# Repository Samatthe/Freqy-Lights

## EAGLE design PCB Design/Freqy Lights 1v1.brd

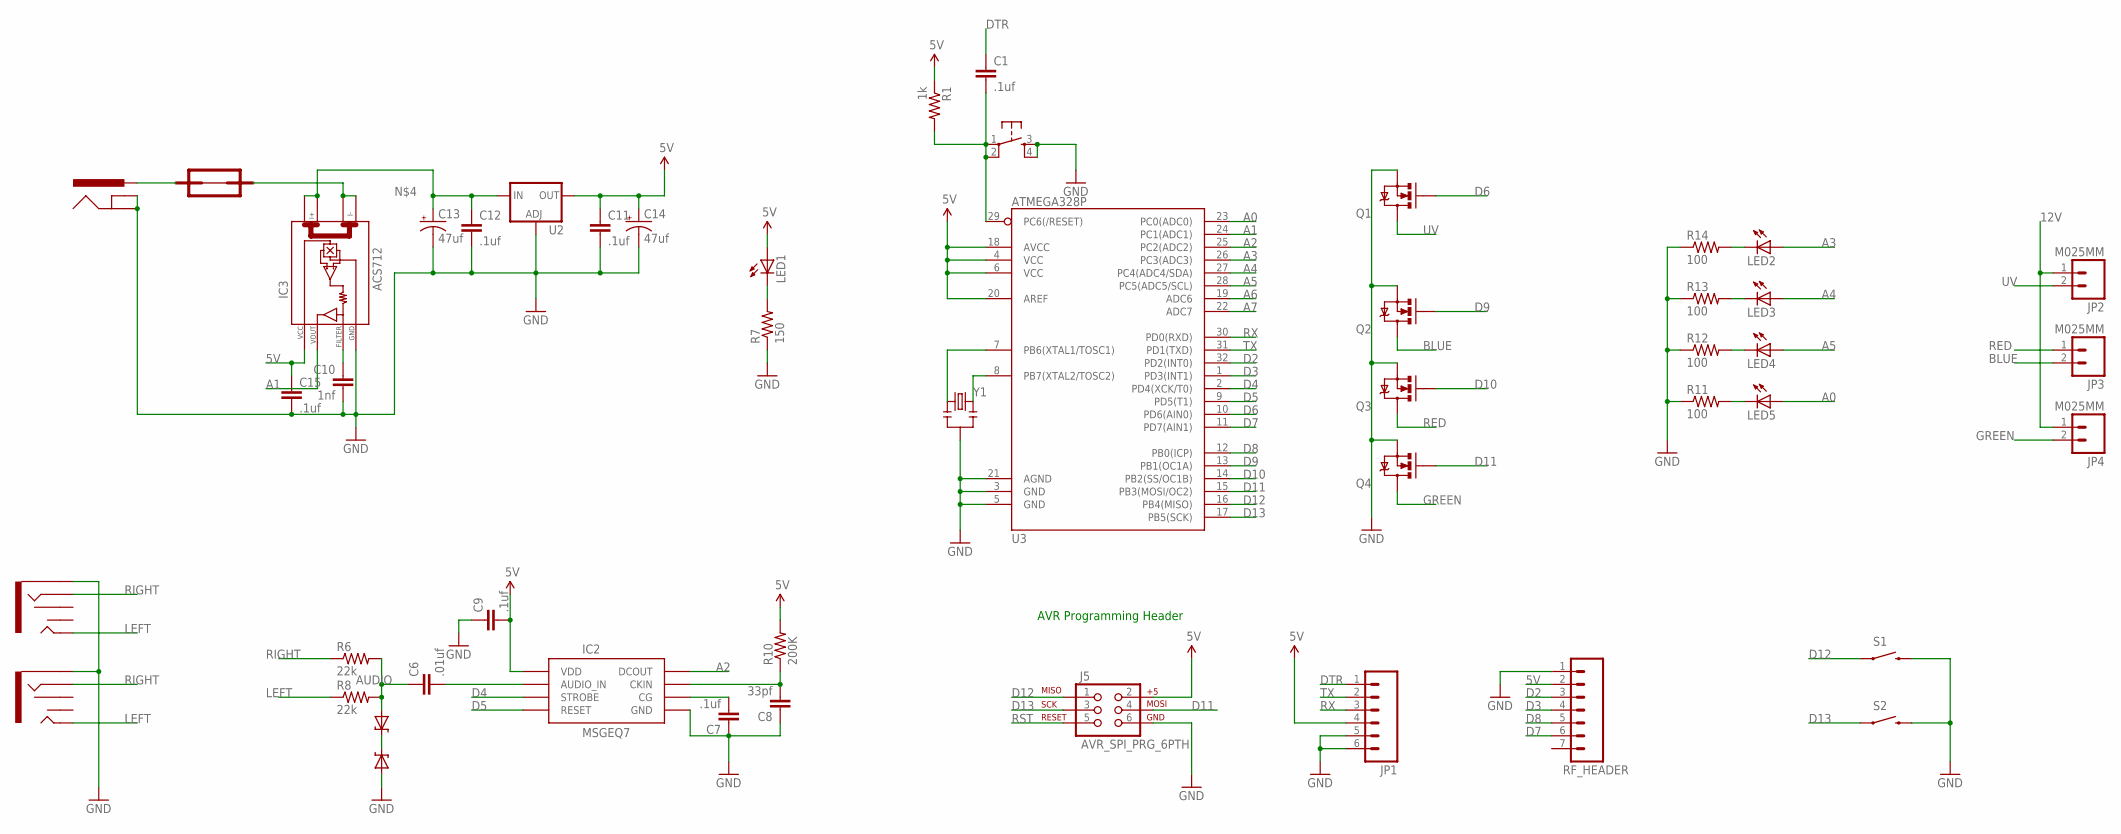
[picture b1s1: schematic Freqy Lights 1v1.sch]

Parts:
AJ1, AJ2: SC1488-1-ND_SMD_AUDIO_3.5; 3.5MM_SMD_AUDIO_SC1488-1-ND
BJ1: CP-202BH-ND_POWERJACK; POWER_JACK_CP-202BH-ND
C1, C7, C9, C11, C12, C15: .1uf; 1206
C6: .01uf; 1206
C8: 33pf; 1206
C10: 1nf; 1206
C13, C14: 47uf; SMD_47UF_CAP_493-2202-1-ND
F1: SSQ12
IC2: MSGEQ7SOIC; SOIC8
IC3: ACS712; SO08
J5: AVR_SPI_PRG_6PTH; 2X3
JP1: M06SIP; 1X06
JP2, JP3, JP4: M025MM; SCREWTERMINAL-5MM-2
LED1, LED2, LED3, LED4, LED5: LED1206; LED-1206
P1: CKN9085CT-ND_SMT_PUSHBUTTON; SMT_PUSHBUTTON_CKN9085CT-ND
Q1, Q2, Q3, Q4: MOSFET-NCHANNELBSS138; SOT23
R1: 1k; 1206
R6, R8: 22k; 1206
R7: 150; 1206
R10: 200K; 1206
R11, R12, R13, R14: 100; 1206
RF_HEADER: M07; 1X07
S1, S2: SWITCH-MOMENTARY-2PTH; TACTILE-PTH
U2: V_REG_317SMD; SOT223
U3: ATMEGA328P; TQFP32-08
U$10, U$11: MM3Z3V3ST1GOSCT-ND_3V_DIODE; 3V_DIODE_MM3Z3V3ST1GOSCT-ND
Y1: RESONATORPTH; RESONATOR-PTH

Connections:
5V: C9.2, C11.1, C14.P$2 (+), C15.1, IC2.1 (VDD), IC3.8 (VCC), J5.2, JP1.4, LED1.A, R1.1, R10.2, RF_HEADER.2, U2.2 (OUT), U3.4 (VCC), U3.6 (VCC), U3.18 (AVCC), U3.20 (AREF)
12V: C12.1, C13.P$2 (+), IC3.1 (I+_0), IC3.2 (I+_1), JP2.1, JP4.1, U2.3 (IN)
A0: LED5.A, U3.23 (PC0(ADC0))
A1: IC3.7 (VOUT), U3.24 (PC1(ADC1))
A2: IC2.3 (DCOUT), U3.25 (PC2(ADC2))
A3: LED2.A, U3.26 (PC3(ADC3))
A4: LED3.A, U3.27 (PC4(ADC4/SDA))
A5: LED4.A, U3.28 (PC5(ADC5/SCL))
A6: U3.19 (ADC6)
A7: U3.22 (ADC7)
AUDIO: C6.1, R6.2, R8.2, U$11.P$2 (A)
BLUE: JP3.2, Q2.3 (D)
D2: RF_HEADER.3, U3.32 (PD2(INT0))
D3: RF_HEADER.4, U3.1 (PD3(INT1))
D4: IC2.4 (STROBE), U3.2 (PD4(XCK/T0))
D5: IC2.7 (RESET), U3.9 (PD5(T1))
D6: Q1.1 (G), U3.10 (PD6(AIN0))
D7: RF_HEADER.6, U3.11 (PD7(AIN1))
D8: RF_HEADER.5, U3.12 (PB0(ICP))
D9: Q2.1 (G), U3.13 (PB1(OC1A))
D10: Q3.1 (G), U3.14 (PB2(SS/OC1B))
D11: J5.4, Q4.1 (G), U3.15 (PB3(MOSI/OC2))
D12: J5.1, S1.1, U3.16 (PB4(MISO))
D13: J5.3, S2.1, U3.17 (PB5(SCK))
DTR: C1.1, JP1.1
GND: AJ1.RING, AJ2.RING, BJ1.GND, BJ1.GNDBRK (GNDBREAK), C7.1, C8.1, C9.1, C10.2, C11.2, C12.2, C13.P$1 (-), C14.P$1 (-), C15.2, IC2.2 (GND), IC3.5 (GND), J5.6, JP1.5, JP1.6, P1.3, P1.4, Q1.2 (S), Q2.2 (S), Q3.2 (S), Q4.2 (S), R7.1, R11.1, R12.1, R13.1, R14.1, RF_HEADER.1, S1.3 (2), S2.3 (2), U2.1 (ADJ), U3.3 (GND), U3.5 (GND), U3.21 (AGND), U$10.P$2 (A), Y1.2
GREEN: JP4.2, Q4.3 (D)
LEFT: AJ1.TIP, AJ2.TIP, R8.1
unnamed: U$10.P$1 (C), U$11.P$1 (C)
unnamed: F1.P$2, IC3.3 (I-_0), IC3.4 (I-_1)
unnamed: C7.2, IC2.6 (CG)
unnamed: C6.2, IC2.5 (AUDIO_IN)
unnamed: LED1.C, R7.2
unnamed: C8.2, IC2.8 (CKIN), R10.1
unnamed: U3.7 (PB6(XTAL1/TOSC1)), Y1.1
unnamed: U3.8 (PB7(XTAL2/TOSC2)), Y1.3
unnamed: C10.1, IC3.6 (FILTER)
unnamed: LED5.C, R11.2
unnamed: LED4.C, R12.2
unnamed: LED3.C, R13.2
unnamed: LED2.C, R14.2
unnamed: BJ1.PWR, F1.P$1
RED: JP3.1, Q3.3 (D)
RIGHT: AJ1.SLEEVE, AJ2.SLEEVE, R6.1
RST: C1.2, J5.5, P1.1, P1.2, R1.2, U3.29 (PC6(/RESET))
RX: JP1.3, U3.30 (PD0(RXD))
TX: JP1.2, U3.31 (PD1(TXD))
UV: JP2.2, Q1.3 (D)

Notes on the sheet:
AVR Programming Header

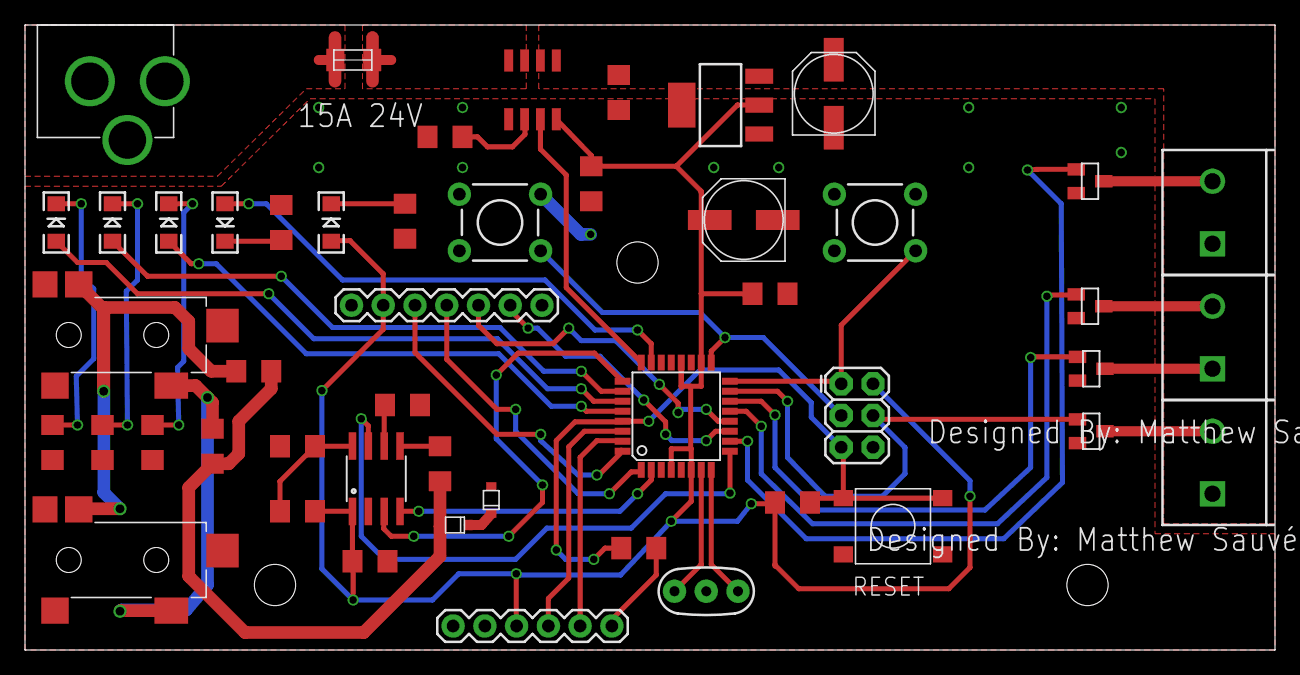
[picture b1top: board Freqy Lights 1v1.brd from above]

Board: 2 copper layers, 100.0 x 50.0 mm, 52 parts (0 on the bottom side), 46 nets.

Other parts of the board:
U$1, U$2, U$3: STAND-OFF

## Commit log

2015-09-14 :octocat: Added .gitattributes & .gitignore files
2015-09-14 First Commit
    Added current program files to repo
2015-09-14 moved files into folder
2015-09-14 renamed the folder
2015-09-14 small change
2015-09-14 small changes
2015-09-14 Revert "small changes"
    This reverts commit ffb5228675db3089b34a67db65559ac9c630ec0b.
2015-09-14 Revert "Revert "small changes""
    This reverts commit ba1f35737dd586a3ee2f63c0124c4f8079821f75.
2015-09-16 added case design files
2015-09-16 changed file names for case top
2015-09-28 added Eagle files to repo

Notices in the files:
parts and their libraries:
SparkFun-DigitalIC: Licensing: CC v3.0 Share-Alike You are welcome to use this library for commercial purposes.
